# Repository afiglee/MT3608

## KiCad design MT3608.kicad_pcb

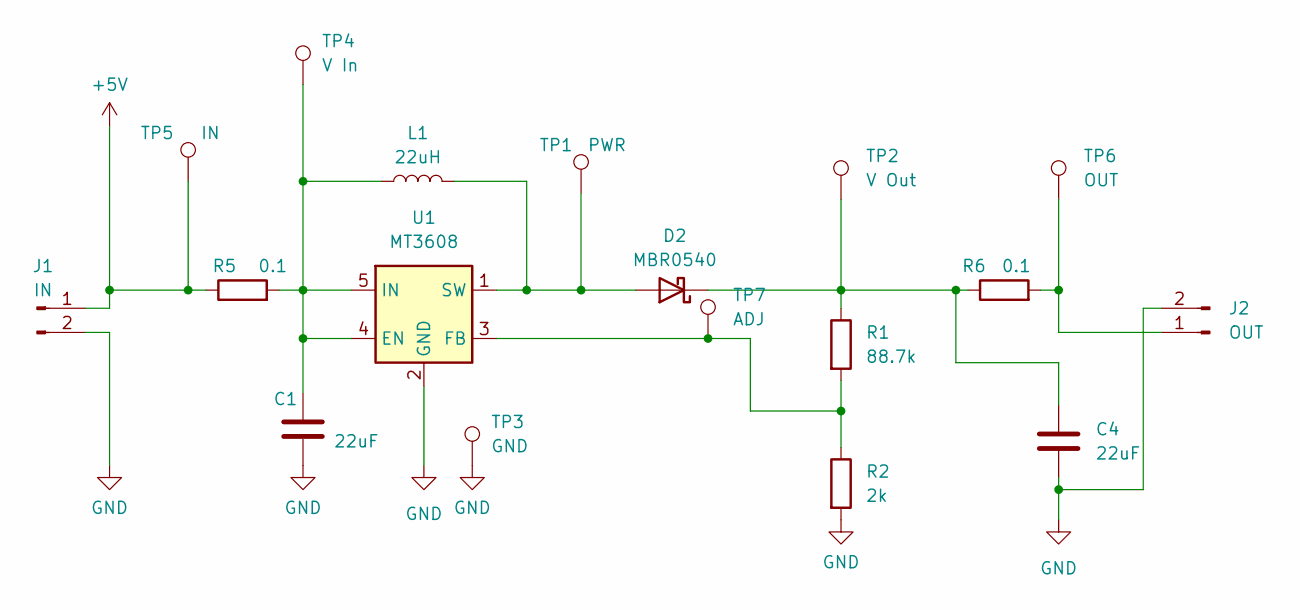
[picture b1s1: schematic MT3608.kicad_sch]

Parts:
C1: 22uF; C_0805_2012Metric_Pad1.18x1.45mm_HandSolder
C4: 22uF; C_1206_3216Metric_Pad1.33x1.80mm_HandSolder
D2: MBR0540; D_SOD-123
J1: IN; PinHeader_1x02_P2.54mm_Vertical
J2: OUT; PinHeader_1x02_P2.54mm_Vertical
L1: 22uH; L_Bourns_SRR1208_12.7x12.7mm
R1: 88.7k; R_0603_1608Metric_Pad0.98x0.95mm_HandSolder
R2: 2k; R_0603_1608Metric_Pad0.98x0.95mm_HandSolder
R5, R6: 0.1; R_0805_2012Metric_Pad1.20x1.40mm_HandSolder
TP1: PWR; Pin_D1.2mm_L11.3mm_W3.0mm_Flat
TP2: V Out; Pin_D1.2mm_L11.3mm_W3.0mm_Flat
TP3: GND; Pin_D1.2mm_L11.3mm_W3.0mm_Flat
TP4: V In; Pin_D1.2mm_L11.3mm_W3.0mm_Flat
TP5: IN; Pin_D1.2mm_L11.3mm_W3.0mm_Flat
TP6: OUT; Pin_D1.2mm_L11.3mm_W3.0mm_Flat
TP7: ADJ; Pin_D1.2mm_L11.3mm_W3.0mm_Flat
U1: MT3608; SOT-23-6

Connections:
+5V: J1.1, R5.1, TP5.1
GND: C1.2, C4.2, J1.2, J2.2, R2.2, TP3.1, U1.2 (GND)
unnamed: D2.2 (A), L1.2, TP1.1, U1.1 (SW)
unnamed: C4.1, D2.1 (K), R1.1, R6.1, TP2.1
unnamed: J2.1, R6.2, TP6.1
unnamed: C1.1, L1.1, R5.2, TP4.1, U1.4 (EN), U1.5 (IN)
unnamed: R1.2, R2.1, TP7.1, U1.3 (FB)

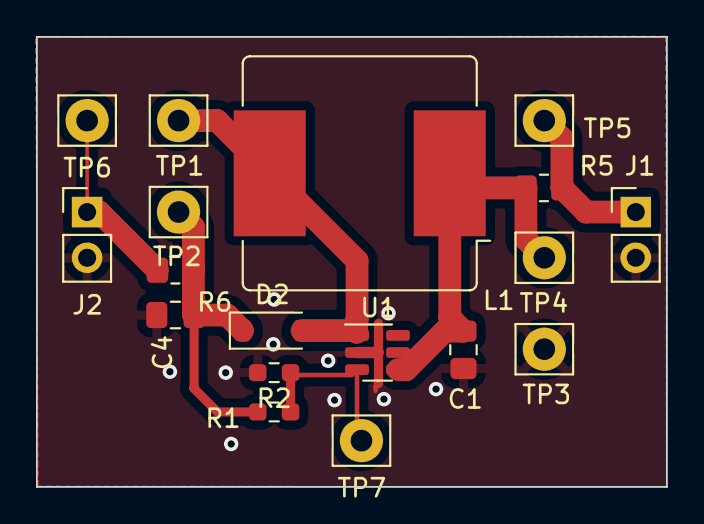
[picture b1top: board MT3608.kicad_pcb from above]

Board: 2 copper layers, 35.0 x 25.0 mm, 18 parts (0 on the bottom side), 7 nets.

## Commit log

2024-04-25 initial
2024-04-25 Take 2
2024-05-13 27V works; corrected TP6
